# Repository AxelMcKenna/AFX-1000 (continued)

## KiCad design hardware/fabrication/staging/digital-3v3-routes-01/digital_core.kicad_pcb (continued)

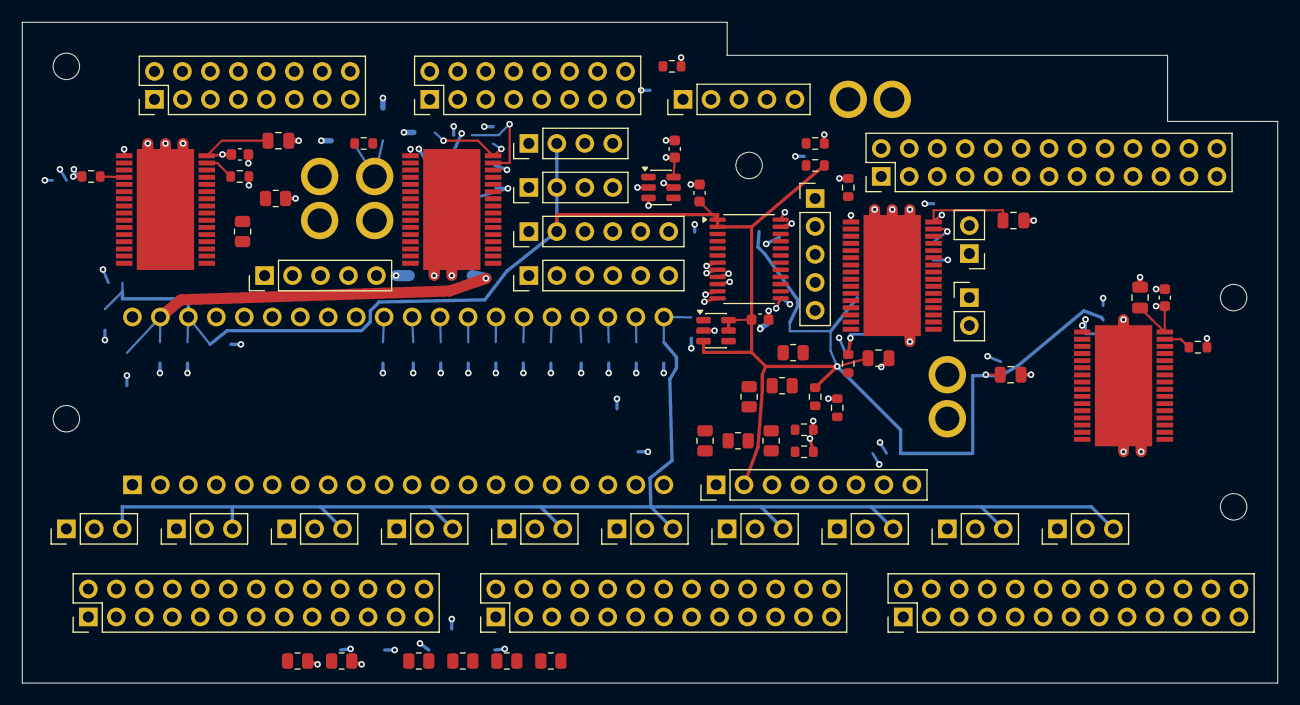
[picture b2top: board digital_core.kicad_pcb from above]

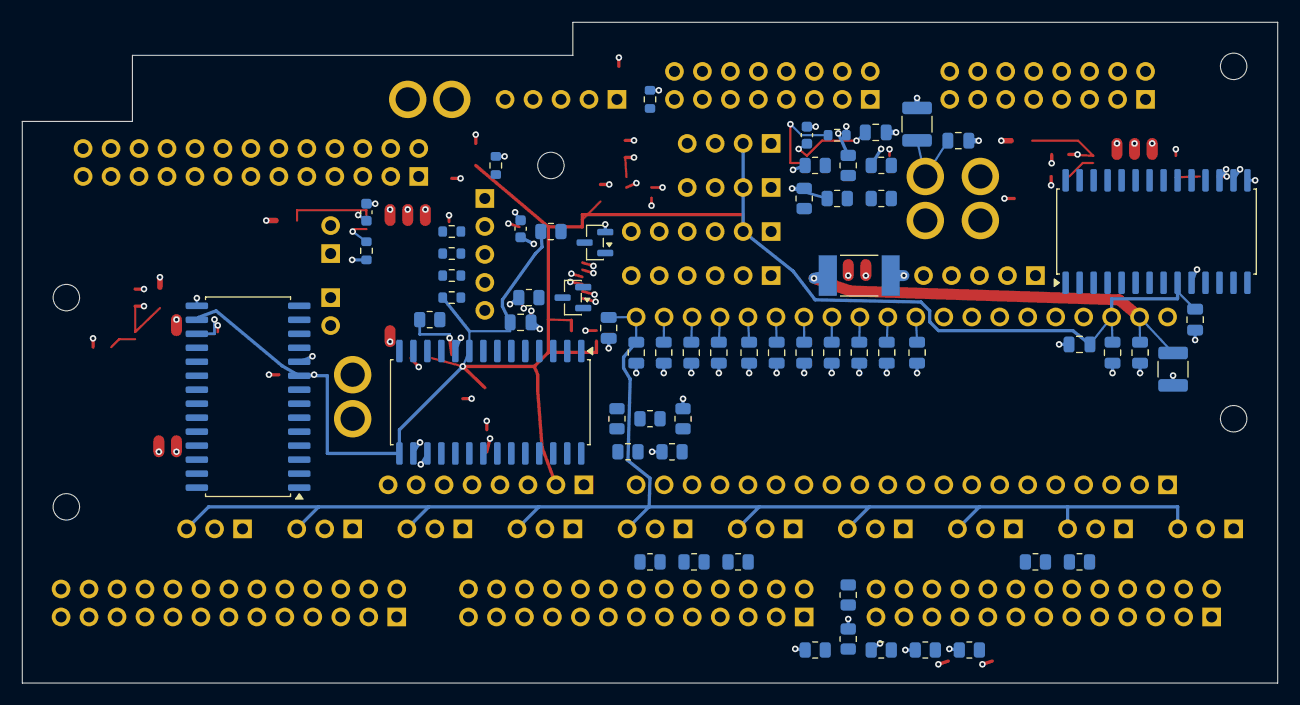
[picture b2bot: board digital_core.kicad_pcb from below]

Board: 4 copper layers, 114.0 x 60.0 mm, 143 parts (63 on the bottom side), 208 nets.

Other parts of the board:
H1, H2, H3, H4, H5: M2_CLEARANCE; M2_Clearance
